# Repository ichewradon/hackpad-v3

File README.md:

# 

My macropad for 3D Modelling with 4x3 keys, 1 rotary encoder.

## Features:
- 12 SK6812 MINI-E LEDs for dynamic LED effects
  - Rainbow / Custom Gradient
  - Music Reactive
  - Static Colour
- 1 EC11 Rotary Encoder to control volume with a custom printed dial
- 12 Individually Addressable Keys
- [KMK Firmware](https://github.com/kmkfw/kmk_firmware) to allow for web-app control and memory after restart

## Overview

This is my hackpad in Fusion360 showing how it's assembled. 

## Case Model

This is my Case Model I made in Fusion360

Bottom side:

Diffuser:

## PCB (Printed Circuit Board)

Here's my PCB. It was made in KiCad. The silkscreen was imported from separate vectors that are in /assets/logos.

Schematic:

PCB:

## BoM (Bill of Materials)
- 12x MX-Style Switches
- 12x DSA Keycaps
- 1x EC11 Rotary Encoder
- 12x 1N4148 Diodes
- 11x SK6812 MINI-E LEDs
- 1x Seeed XIAO RP2040

<div align="center">
  
</div>

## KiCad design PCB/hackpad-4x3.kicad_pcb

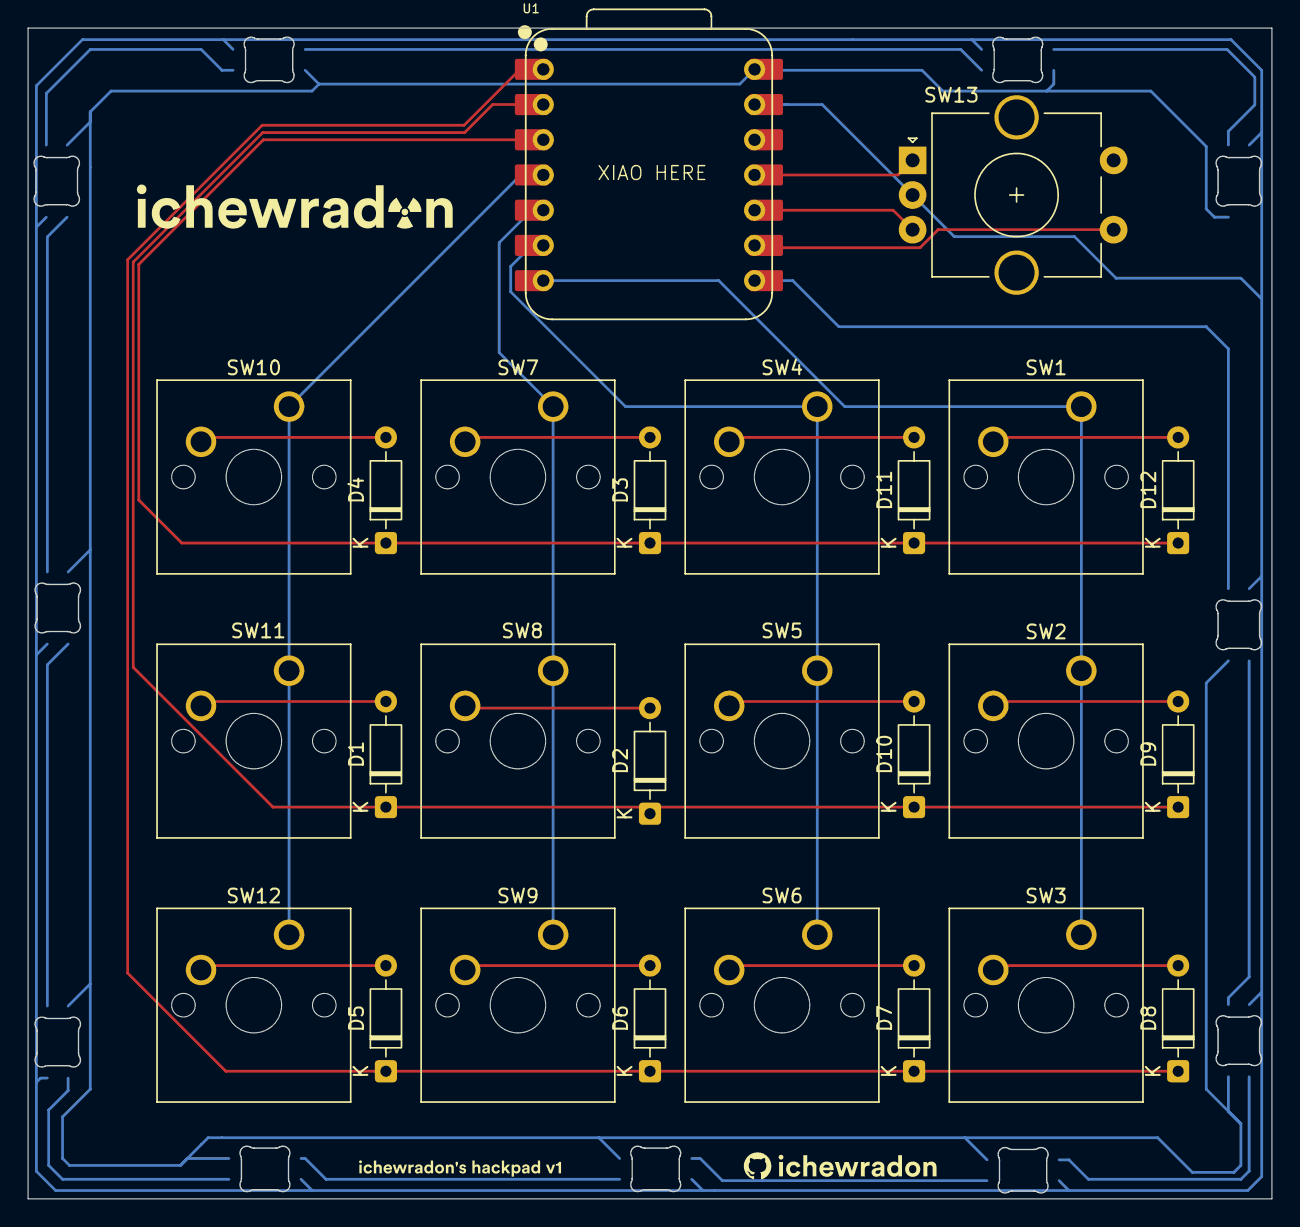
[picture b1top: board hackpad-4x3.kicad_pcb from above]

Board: 2 copper layers, 89.7 x 84.4 mm, 37 parts (0 on the bottom side), 24 nets.

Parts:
D1, D2, D3, D4, D5, D6, D7, D8, D9, D10, D11, D12: 1N4148; D_DO-35_SOD27_P7.62mm_Horizontal
D13, D13#2, D13#3, D14, D16, D17, D17#2, D19, D22, D22#2, D22#3: SK6812-E; MX_SK6812MINI-E_REV
SW1, SW2, SW3, SW4, SW5, SW6, SW7, SW8, SW9, SW10, SW11, SW12: SW_Push; SW_Cherry_MX_1.00u_PCB
SW13: RotaryEncoder_Switch; RotaryEncoder_Alps_EC11E-Switch_Vertical_H20mm_CircularMoun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
U1: XIAO-RP2040-DIP

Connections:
/5V: D13.1 (VDD), D13#2.1 (VDD), D13#3.1 (VDD), D14.1 (VDD), D16.1 (VDD), D17.1 (VDD), D17#2.1 (VDD), D19.1 (VDD), D22.1 (VDD), D22#2.1 (VDD), D22#3.1 (VDD), U1.14 (VBUS)
/BTN1: SW13.S1, U1.9 (GPIO2/SCK)
/COL1: SW10.1, SW11.1, SW12.1, U1.4 (GPIO29/ADC3/A3)
/COL2: SW7.1, SW8.1, SW9.1, U1.5 (GPIO6/SDA)
/COL3: SW4.1, SW5.1, SW6.1, U1.6 (GPIO7/SCL)
/COL4: SW1.1, SW2.1, SW3.1, U1.7 (GPIO0/TX)
/GND: D13.3 (GND), D13#2.3 (GND), D13#3.3 (GND), D14.3 (GND), D16.3 (GND), D17.3 (GND), D17#2.3 (GND), D19.3 (GND), D22.3 (GND), D22#2.3 (GND), D22#3.3 (GND), SW13.C, U1.13 (GND)
/ROT1: SW13.A, U1.11 (GPIO3/MOSI)
/ROT2: SW13.B, U1.10 (GPIO4/MISO)
/ROW1: D3.1 (K), D4.1 (K), D11.1 (K), D12.1 (K), U1.3 (GPIO28/ADC2/A2)
/ROW2: D1.1 (K), D2.1 (K), D9.1 (K), D10.1 (K), U1.2 (GPIO27/ADC1/A1)
/ROW3: D5.1 (K), D6.1 (K), D7.1 (K), D8.1 (K), U1.1 (GPIO26/ADC0/A0)
unnamed: D1.2 (A), SW11.2
unnamed: D2.2 (A), SW8.2
unnamed: D3.2 (A), SW7.2
unnamed: D4.2 (A), SW10.2
unnamed: D5.2 (A), SW12.2
unnamed: D6.2 (A), SW9.2
unnamed: D7.2 (A), SW6.2
unnamed: D8.2 (A), SW3.2
unnamed: D9.2 (A), SW2.2
unnamed: D10.2 (A), SW5.2
unnamed: D11.2 (A), SW4.2
unnamed: D12.2 (A), SW1.2

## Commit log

2025-12-01 Initialize README with project description
    Add project description for hackpad.
2025-12-06 Update README to remove RGB backlight reference
    Removed mention of RGB backlight from the description.
2025-12-06 Create 1
2025-12-06 Rename PCB.png to assets/PCB.png
2025-12-06 Rename Schematics.png to assets/Schematics.png
2025-12-06 Rename hackpad-4x3.kicad_pcb to PCB/hackpad-4x3.kicad_pcb
2025-12-06 Rename hackpad-4x3.kicad_prl to PCB/hackpad-4x3.kicad_prl
2025-12-06 Rename hackpad-4x3.kicad_pro to PCB/hackpad-4x3.kicad_pro
2025-12-06 Rename hackpad-4x3.kicad_sch to PCB/hackpad-4x3.kicad_sch
2025-12-06 Add logo image to README
2025-12-06 Update README formatting for title and logo
2025-12-06 Adjust header formatting in README.md
2025-12-06 Update README header format and logo position
2025-12-06 Add PCB section to README
    Added a section about the PCB design created in KiCad.
2025-12-07 Fix image paths and add schematics to README
    Updated image paths and added schematics section.
2025-12-07 Update project name logo in README
2025-12-07 Fix logo path case sensitivity in README.md
2025-12-07 Fix image paths and update README section titles
    Corrected logo image paths and updated section titles.
2025-12-07 Rename logo file to lowercase path
2025-12-07 Add logo.svg to assets/logos directory
2025-12-07 Fix file path casing for projectname.svg
2025-12-07 Add CAD Model section to README
    Added a section for the CAD model created in Fusion360.
2025-12-07 Revise README for case model and PCB details
    Updated section headers and improved image captions for clarity.
2025-12-07 Add image for diffuser in README
2025-12-07 Update LED count from 12 to 11 in README
2025-12-07 Update BoM section title to 'Bill of Materials'
2025-12-07 Refactor README sections and update images
    Updated README to improve structure and clarity.
